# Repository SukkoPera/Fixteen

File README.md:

# Fixteen
Fixteen is an Open Hardware internal 64 kB RAM Expansion board for the Commodore 16.

## Summary
Since [expanding the C16 to 64 kB through the cartridge port is impossible](https://github.com/SukkoPera/OpenC16RamExpansion), I decided to develop an internal solution that would be as easy as it could get.

Fixteen is exactly that: open your C16, sandwich the board between the TED (U1) and its socket and your C16 will instantly be upgraded to 64 kilobytes of RAM, gaining compatibility with all the software developed for the Plus/4!

Fixteen works by redirecting all RAM access to two onboard chips, therefore it can also be used to repair mainboards with failed RAM chips and/or multiplexers.

If for any reason you want to go back to 16 kB, just toggle the J2 jumper: Fixteen will be deactivated and the mainboard RAM will be back in business.

## Design and Assembly Notes
This project uses some SMD components due to space constraints, you are recommended to solder those first.

U2 and U3 can either be 74x157 or 74x257, as they are permanently enabled. I recommend using chips from the HCT family, but LS will do. Do NOT use HC.

The actual 4464 RAM chips have been out of production for ages but they can be bought supercheap on AliExpress & similar sites, making this board very affordable to build for everyone. Let's say 10€? So get them second-hand and be happy :).

U6 and U7 are not related to the RAM expansion and are optional: they provide protection for the TED from ESD (Electrostatic Discharge) coming in through the joystick ports (which is one of the most common causes of TED failures). I had some space on the board and thought they would be a nice addition but they are small components, so just don't bother soldering them if you don't feel comfortable doing it.

You can connect a switch to U2 if you want to be able to switch back to 16 kB without having to open the case again. Honestly I just wouldn't bother, there is virtually no software that requires no more than 16 kB and it should just be fixed if this is really the case.

The board was accurately sized to fit alongside the CPU in a C16, but if you are using a CPU replacement it might just not physically fit. The same applies if you are using a Commodore 116, on which the board is not tested but it should theoretically work. I am sorry for that, feel free to redesign it and adjust the shape accordingly, it's easy to do with open source hardware.

## Releases
If you want to get this board produced, you are recommended to get [the latest release](https://github.com/SukkoPera/Fixteen/releases) rather than the current git version, as the latter might be under development and is not guaranteed to be working.

Every release is accompanied by its Bill Of Materials (BOM) file and any relevant notes about it, which you are recommended to read carefully.

## License
The Fixteen documentation, including the design itself, is copyright &copy; SukkoPera 2023 and is licensed under the [CERN OHL v. 1.2](https://ohwr.org/project/cernohl/wikis/Documents/CERN-OHL-version-1.2).

This documentation is distributed *as is* and WITHOUT ANY EXPRESS OR IMPLIED WARRANTIES whatsoever with respect to its functionality, operability or use, including, without limitation, any implied warranties OF MERCHANTABILITY, SATISFACTORY QUALITY, FITNESS FOR A PARTICULAR PURPOSE or infringement. We expressly disclaim any liability whatsoever for any direct, indirect, consequential, incidental or special damages, including, without limitation, lost revenues, lost profits, losses resulting from business interruption or loss of data, regardless of the form of action or legal theory under which the liability may be asserted, even if advised of the possibility or likelihood of such damages.

## Support the Project
If you want to get some boards manufactured, you can get them from PCBWay through this link:

You get my gratitude and cheap, professionally-made and good quality PCBs, I get some credit that will help with this and [other projects](https://www.pcbway.com/project/member/?bmbno=72D33927-5EF6-42). You won't even have to worry about the various PCB options, it's all pre-configured for you!

Also, if you still have to register, [you can use this link](https://www.pcbway.com/setinvite.aspx?inviteid=41100) to get some bonus initial credit (and yield me some more).

You can also buy me a coffee if you want:

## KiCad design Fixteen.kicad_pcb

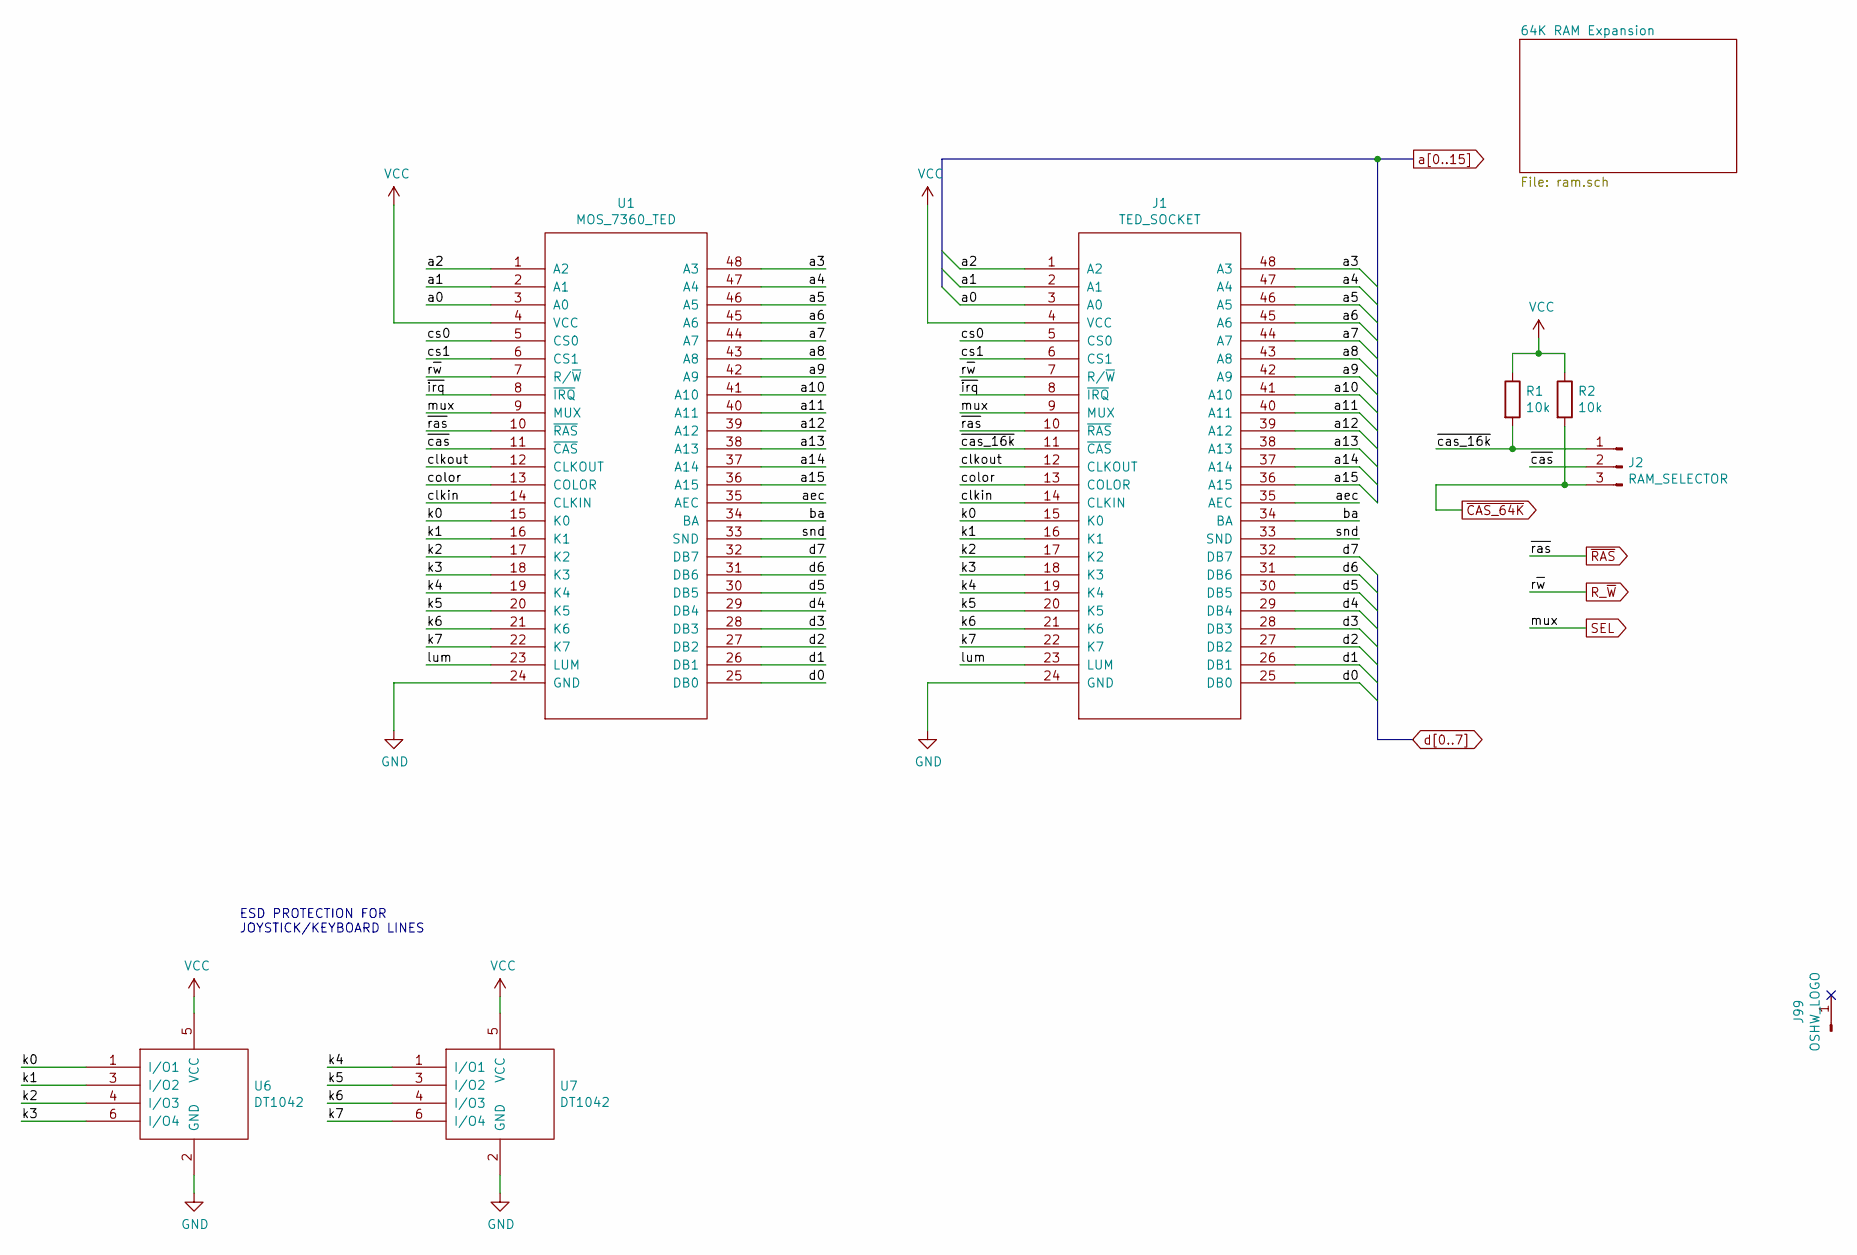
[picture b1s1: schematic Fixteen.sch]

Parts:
J1: TED_SOCKET; DIP-48_W15.24mm_LongPads_ModSilkS
J2: RAM_SELECTOR; Pin_Header_Straight_1x03-ModSilkS
J99: OSHW_LOGO; OSHW-Logo_5.7x6mm_Copper
R1, R2: 10k; R_0805_2012Metric_Pad1.20x1.40mm_HandSolder; LCSC C17414
U1: MOS_7360_TED; DIP-48_W15.24mm_Socket_LongPads
U6, U7: DT1042; TSOP-6_1.65x3.05mm_P0.95mm; MouserPN 621-DT1042-04TS-7; LCSC C460064

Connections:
/aec: J1.35 (AEC), U1.35 (AEC)
/ba: J1.34 (BA), U1.34 (BA)
/clkin: J1.14 (CLKIN), U1.14 (CLKIN)
/clkout: J1.12 (CLKOUT), U1.12 (CLKOUT)
/color: J1.13 (COLOR), U1.13 (COLOR)
/cs0: J1.5 (CS0), U1.5 (CS0)
/cs1: J1.6 (CS1), U1.6 (CS1)
/k0: J1.15 (K0), U1.15 (K0), U6.1 (I/O1)
/k1: J1.16 (K1), U1.16 (K1), U6.3 (I/O2)
/k2: J1.17 (K2), U1.17 (K2), U6.4 (I/O3)
/k3: J1.18 (K3), U1.18 (K3), U6.6 (I/O4)
/k4: J1.19 (K4), U1.19 (K4), U7.1 (I/O1)
/k5: J1.20 (K5), U1.20 (K5), U7.3 (I/O2)
/k6: J1.21 (K6), U1.21 (K6), U7.4 (I/O3)
/k7: J1.22 (K7), U1.22 (K7), U7.6 (I/O4)
/lum: J1.23 (LUM), U1.23 (LUM)
/snd: J1.33 (SND), U1.33 (SND)
/~cas: J2.2, U1.11 (~CAS)
/~cas_16k: J1.11 (~CAS), J2.1, R1.2
/~irq: J1.8 (~IRQ), U1.8 (~IRQ)
GND: J1.24 (GND), U1.24 (GND), U6.2 (GND), U7.2 (GND); also elsewhere on the board
R_~W: J1.7 (R/~W), U1.7 (R/~W); also elsewhere on the board
SEL: J1.9 (MUX), U1.9 (MUX); also elsewhere on the board
VCC: J1.4 (VCC), R1.1, R2.1, U1.4 (VCC), U6.5 (VCC), U7.5 (VCC); also elsewhere on the board
a0: J1.3 (A0), U1.3 (A0); also elsewhere on the board
a1: J1.2 (A1), U1.2 (A1); also elsewhere on the board
a2: J1.1 (A2), U1.1 (A2); also elsewhere on the board
a3: J1.48 (A3), U1.48 (A3); also elsewhere on the board
a4: J1.47 (A4), U1.47 (A4); also elsewhere on the board
a5: J1.46 (A5), U1.46 (A5); also elsewhere on the board
a6: J1.45 (A6), U1.45 (A6); also elsewhere on the board
a7: J1.44 (A7), U1.44 (A7); also elsewhere on the board
a8: J1.43 (A8), U1.43 (A8); also elsewhere on the board
a9: J1.42 (A9), U1.42 (A9); also elsewhere on the board
a10: J1.41 (A10), U1.41 (A10); also elsewhere on the board
a11: J1.40 (A11), U1.40 (A11); also elsewhere on the board
a12: J1.39 (A12), U1.39 (A12); also elsewhere on the board
a13: J1.38 (A13), U1.38 (A13); also elsewhere on the board
a14: J1.37 (A14), U1.37 (A14); also elsewhere on the board
a15: J1.36 (A15), U1.36 (A15); also elsewhere on the board
d0: J1.25 (DB0), U1.25 (DB0); also elsewhere on the board
d1: J1.26 (DB1), U1.26 (DB1); also elsewhere on the board
d2: J1.27 (DB2), U1.27 (DB2); also elsewhere on the board
d3: J1.28 (DB3), U1.28 (DB3); also elsewhere on the board
d4: J1.29 (DB4), U1.29 (DB4); also elsewhere on the board
d5: J1.30 (DB5), U1.30 (DB5); also elsewhere on the board
d6: J1.31 (DB6), U1.31 (DB6); also elsewhere on the board
d7: J1.32 (DB7), U1.32 (DB7); also elsewhere on the board
~CAS_64K: J2.3, R2.2; also elsewhere on the board
~RAS: J1.10 (~RAS), U1.10 (~RAS); also elsewhere on the board

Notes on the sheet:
ESD PROTECTION FOR JOYSTICK/KEYBOARD LINES

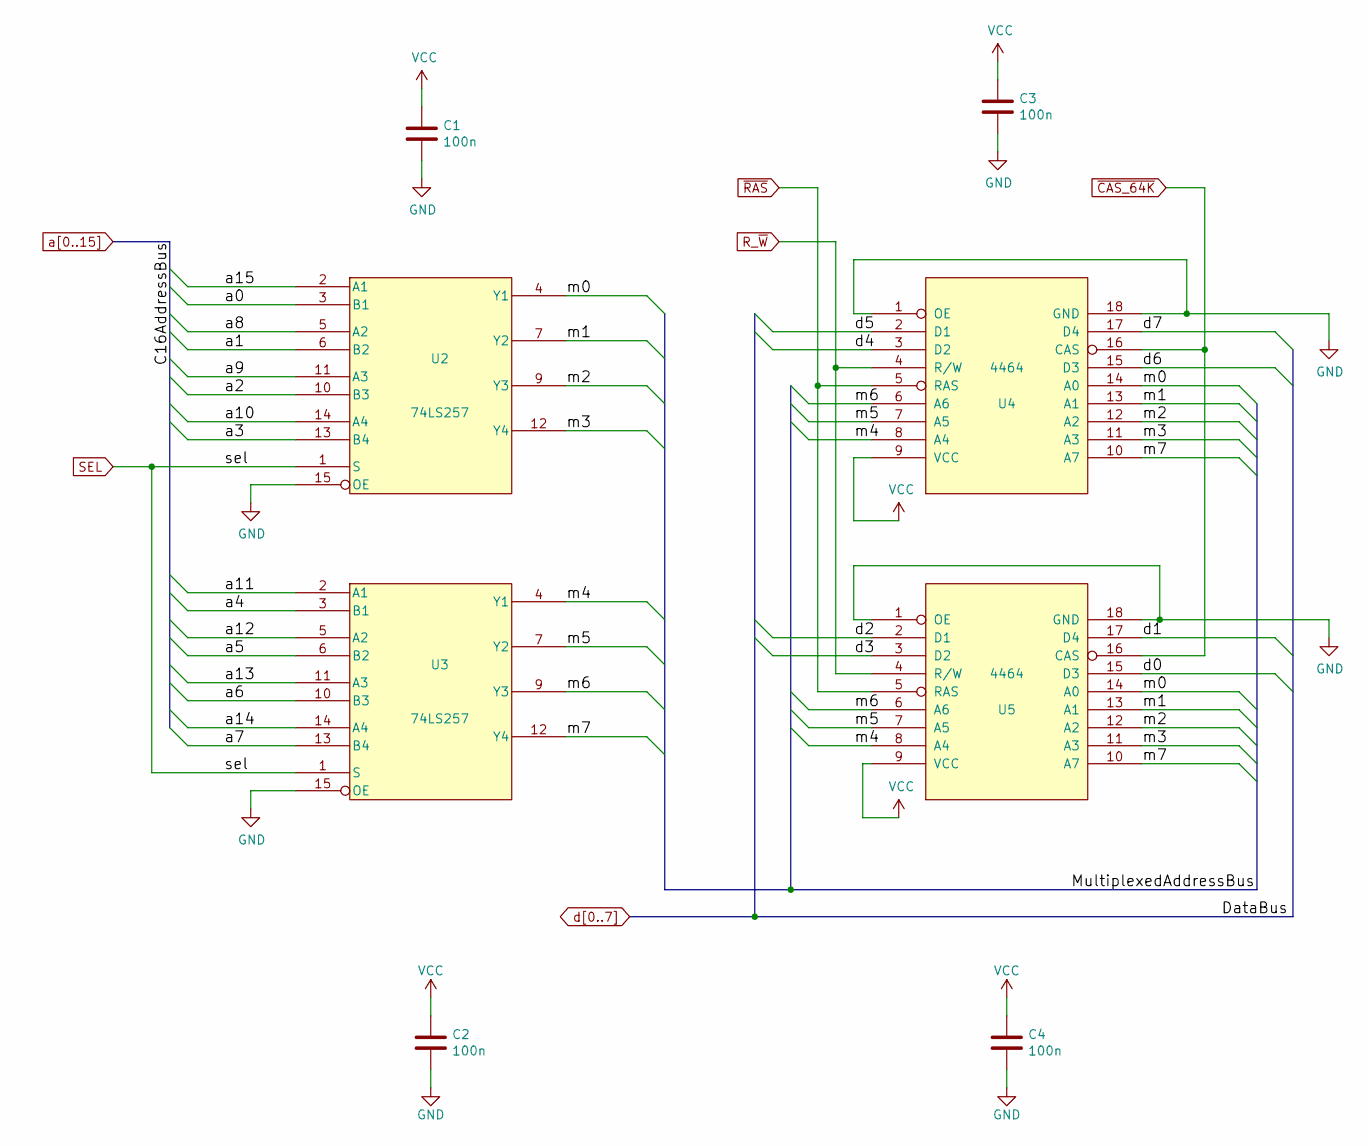
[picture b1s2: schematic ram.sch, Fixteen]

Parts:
C1, C2, C3, C4: 100n; C_0805_2012Metric_Pad1.18x1.45mm_HandSolder; LCSC C49678
U2, U3: 74LS257; SOIC-16_3.9x9.9mm_P1.27mm; LCSC C707097
U4, U5: 4464; DIP-18_W7.62mm_Socket_LongPads

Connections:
/64K RAM Expansion/m0: U2.4 (Y1), U4.14 (A0), U5.14 (A0)
/64K RAM Expansion/m1: U2.7 (Y2), U4.13 (A1), U5.13 (A1)
/64K RAM Expansion/m2: U2.9 (Y3), U4.12 (A2), U5.12 (A2)
/64K RAM Expansion/m3: U2.12 (Y4), U4.11 (A3), U5.11 (A3)
/64K RAM Expansion/m4: U3.4 (Y1), U4.8 (A4), U5.8 (A4)
/64K RAM Expansion/m5: U3.7 (Y2), U4.7 (A5), U5.7 (A5)
/64K RAM Expansion/m6: U3.9 (Y3), U4.6 (A6), U5.6 (A6)
/64K RAM Expansion/m7: U3.12 (Y4), U4.10 (A7), U5.10 (A7)
GND: C1.2, C2.2, C3.2, C4.2, U2.8 (GND), U2.15 (OE), U3.8 (GND), U3.15 (OE), U4.1 (OE), U4.18 (GND), U5.1 (OE), U5.18 (GND); also elsewhere on the board
R_~W: U4.4 (R/W), U5.4 (R/W); also elsewhere on the board
SEL: U2.1 (S), U3.1 (S); also elsewhere on the board
VCC: C1.1, C2.1, C3.1, C4.1, U2.16 (VCC), U3.16 (VCC), U4.9 (VCC), U5.9 (VCC); also elsewhere on the board
a0: U2.3 (B1); also elsewhere on the board
a1: U2.6 (B2); also elsewhere on the board
a2: U2.10 (B3); also elsewhere on the board
a3: U2.13 (B4); also elsewhere on the board
a4: U3.3 (B1); also elsewhere on the board
a5: U3.6 (B2); also elsewhere on the board
a6: U3.10 (B3); also elsewhere on the board
a7: U3.13 (B4); also elsewhere on the board
a8: U2.5 (A2); also elsewhere on the board
a9: U2.11 (A3); also elsewhere on the board
a10: U2.14 (A4); also elsewhere on the board
a11: U3.2 (A1); also elsewhere on the board
a12: U3.5 (A2); also elsewhere on the board
a13: U3.11 (A3); also elsewhere on the board
a14: U3.14 (A4); also elsewhere on the board
a15: U2.2 (A1); also elsewhere on the board
d0: U5.15 (D3); also elsewhere on the board
d1: U5.17 (D4); also elsewhere on the board
d2: U5.2 (D1); also elsewhere on the board
d3: U5.3 (D2); also elsewhere on the board
d4: U4.3 (D2); also elsewhere on the board
d5: U4.2 (D1); also elsewhere on the board
d6: U4.15 (D3); also elsewhere on the board
d7: U4.17 (D4); also elsewhere on the board
~CAS_64K: U4.16 (CAS), U5.16 (CAS); also elsewhere on the board
~RAS: U4.5 (RAS), U5.5 (RAS); also elsewhere on the board

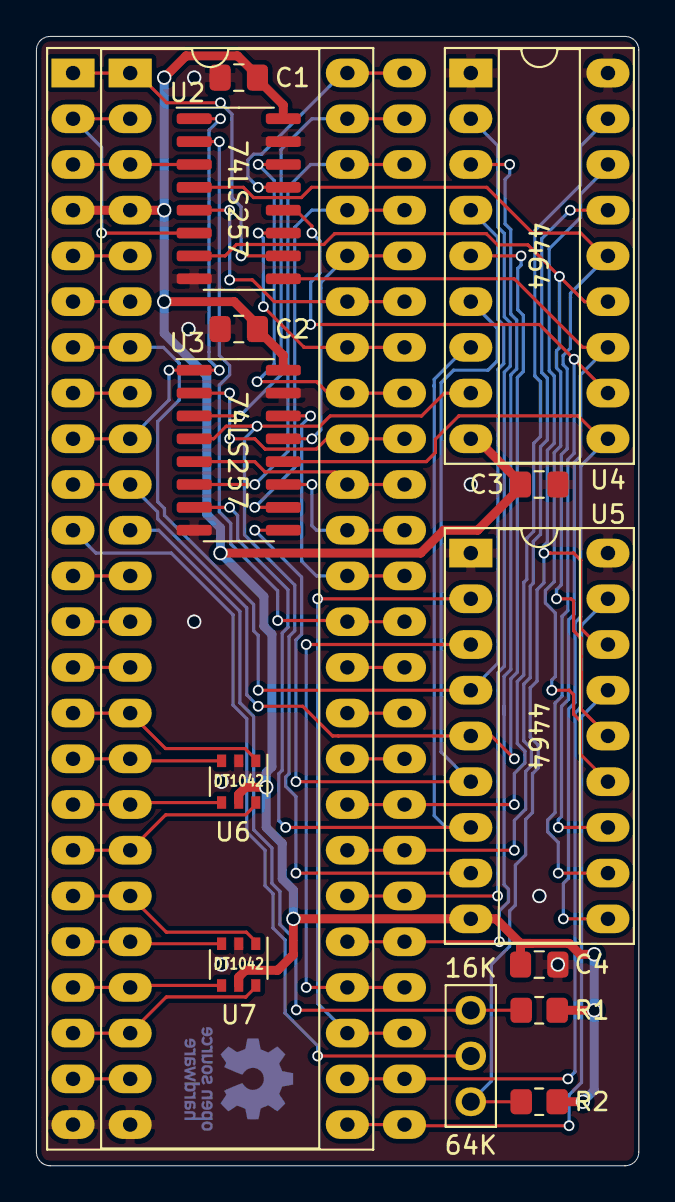
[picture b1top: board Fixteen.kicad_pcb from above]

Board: 2 copper layers, 33.5 x 62.7 mm, 16 parts (1 on the bottom side), 58 nets.

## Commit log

2020-11-28 Add ESD protection (?) Found all of this stuff uncommitted after months... :|
2020-11-29 Turned this into a ESD protection + 64k internal RAM expansion
2020-11-29 Remove fp-info-cache
2020-11-30 Set solder_mask_min_width to 0
2020-12-28 Redo connections as they are on OpenC16RamExpansion V2 did not work :(
2020-12-28 Ready for V3
2023-12-27 Cut corner, for the thing to hopefully fit with MCes's CPU4C16 - Untested!
2023-12-27 Finalize release
2023-12-27 Add README
2023-12-27 Add license statement, project URL and version number

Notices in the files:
Fixteen.kicad_pcb:
Licensed under CERN OHL v.1.2
